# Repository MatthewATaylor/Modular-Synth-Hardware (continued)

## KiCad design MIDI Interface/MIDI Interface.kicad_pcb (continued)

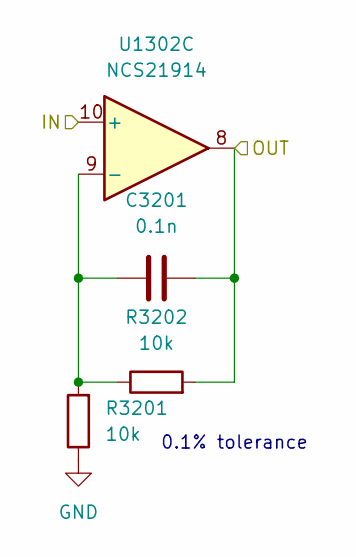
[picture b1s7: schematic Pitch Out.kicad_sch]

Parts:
C3201: 0.1n; C_Disc_D5.5mm_W2.5mm_P2.50mm
R3201, R3202: 10k; R_Axial_DIN0207_L6.3mm_D2.5mm_P7.62mm_Horizontal
U1302: NCS21914; SOIC-14_3.9x8.7mm_P1.27mm

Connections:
/Pitch/Out1/IN: U1302.5 (+); also elsewhere on the board
/Pitch/Out1/OUT: U1302.7; also elsewhere on the board
/Pitch/Out2/IN: U1302.10 (+); also elsewhere on the board
/Pitch/Out2/OUT: C3201.2, R3202.2, U1302.8; also elsewhere on the board
/Pitch/Out3/IN: U1302.12 (+); also elsewhere on the board
/Pitch/Out3/OUT: U1302.14; also elsewhere on the board
/Pitch/Out/IN: U1302.3 (+); also elsewhere on the board
/Pitch/Out/OUT: U1302.1; also elsewhere on the board
GND: R3201.1; also elsewhere on the board
unnamed 163: U1302.2 (-); also elsewhere on the board
unnamed 164: U1302.6 (-); also elsewhere on the board
unnamed: C3201.1, R3201.2, R3202.1, U1302.9 (-)
unnamed 166: U1302.13 (-); also elsewhere on the board

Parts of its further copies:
C3001, C3101, C3301, C3401, C3501, C3601, C3701: 0.1n; C_Disc_D5.5mm_W2.5mm_P2.50mm
R3001, R3002, R3101, R3102, R3301, R3302, R3401, R3402, R3501, R3502, R3601, R3602, R3701, R3702: 10k; R_Axial_DIN0207_L6.3mm_D2.5mm_P7.62mm_Horizontal

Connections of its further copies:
/Pitch/Out1/OUT: C3101.2, R3102.2; also elsewhere on the board
/Pitch/Out3/OUT: C3301.2, R3302.2; also elsewhere on the board
/Pitch/Out4/OUT: C3401.2, R3402.2; also elsewhere on the board
/Pitch/Out5/OUT: C3501.2, R3502.2; also elsewhere on the board
/Pitch/Out6/OUT: C3601.2, R3602.2; also elsewhere on the board
/Pitch/Out7/OUT: C3701.2, R3702.2; also elsewhere on the board
/Pitch/Out/OUT: C3001.2, R3002.2; also elsewhere on the board
GND: R3001.1, R3101.1, R3301.1, R3401.1, R3501.1, R3601.1, R3701.1; also elsewhere on the board
unnamed 163: C3001.1, R3001.2, R3002.1; also elsewhere on the board
unnamed 164: C3101.1, R3101.2, R3102.1; also elsewhere on the board
unnamed 166: C3301.1, R3301.2, R3302.1; also elsewhere on the board
unnamed 167: C3401.1, R3401.2, R3402.1; also elsewhere on the board
unnamed 168: C3501.1, R3501.2, R3502.1; also elsewhere on the board
unnamed 169: C3601.1, R3601.2, R3602.1; also elsewhere on the board
unnamed 170: C3701.1, R3701.2, R3702.1; also elsewhere on the board

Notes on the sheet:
0.1% tolerance

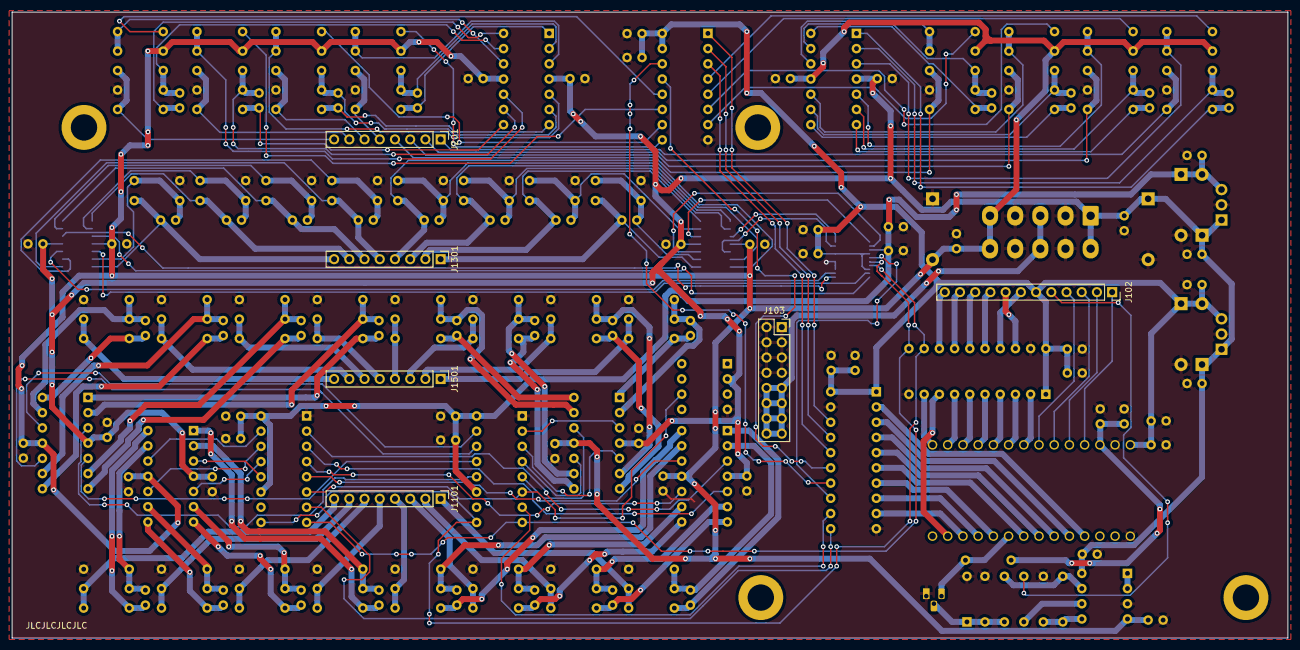
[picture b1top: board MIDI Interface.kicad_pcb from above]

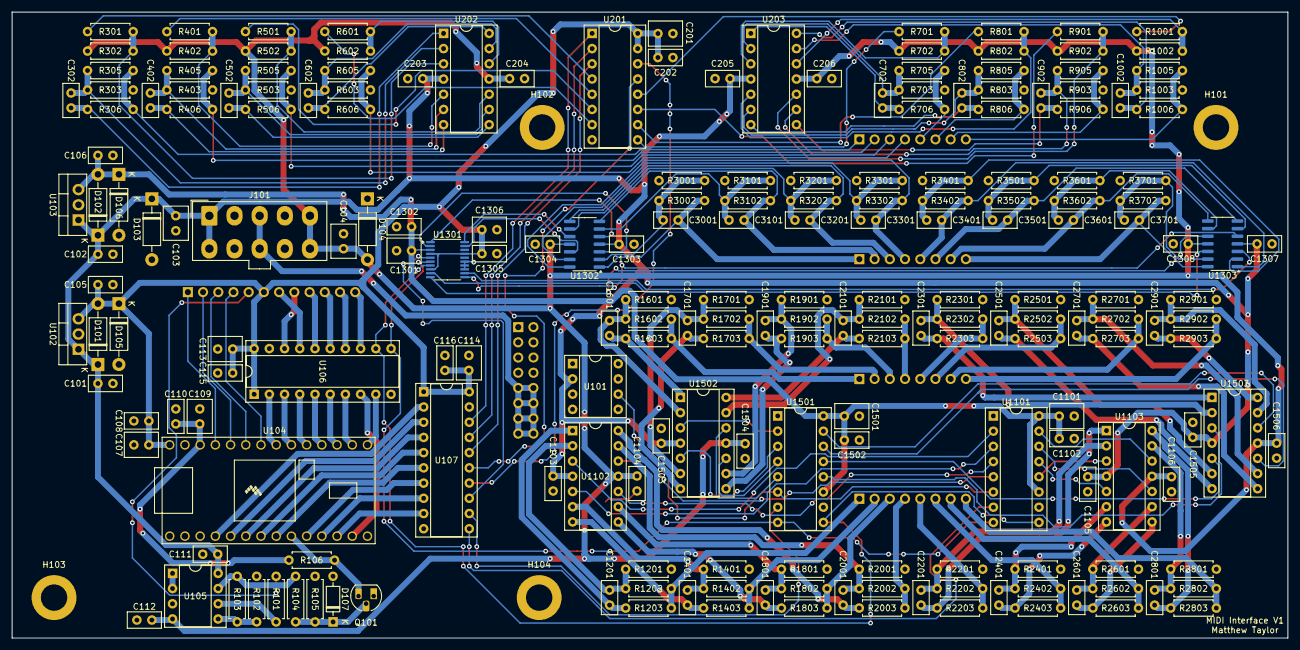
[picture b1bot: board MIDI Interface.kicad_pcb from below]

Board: 2 copper layers, 213.0 x 104.5 mm, 222 parts (216 on the bottom side), 179 nets.

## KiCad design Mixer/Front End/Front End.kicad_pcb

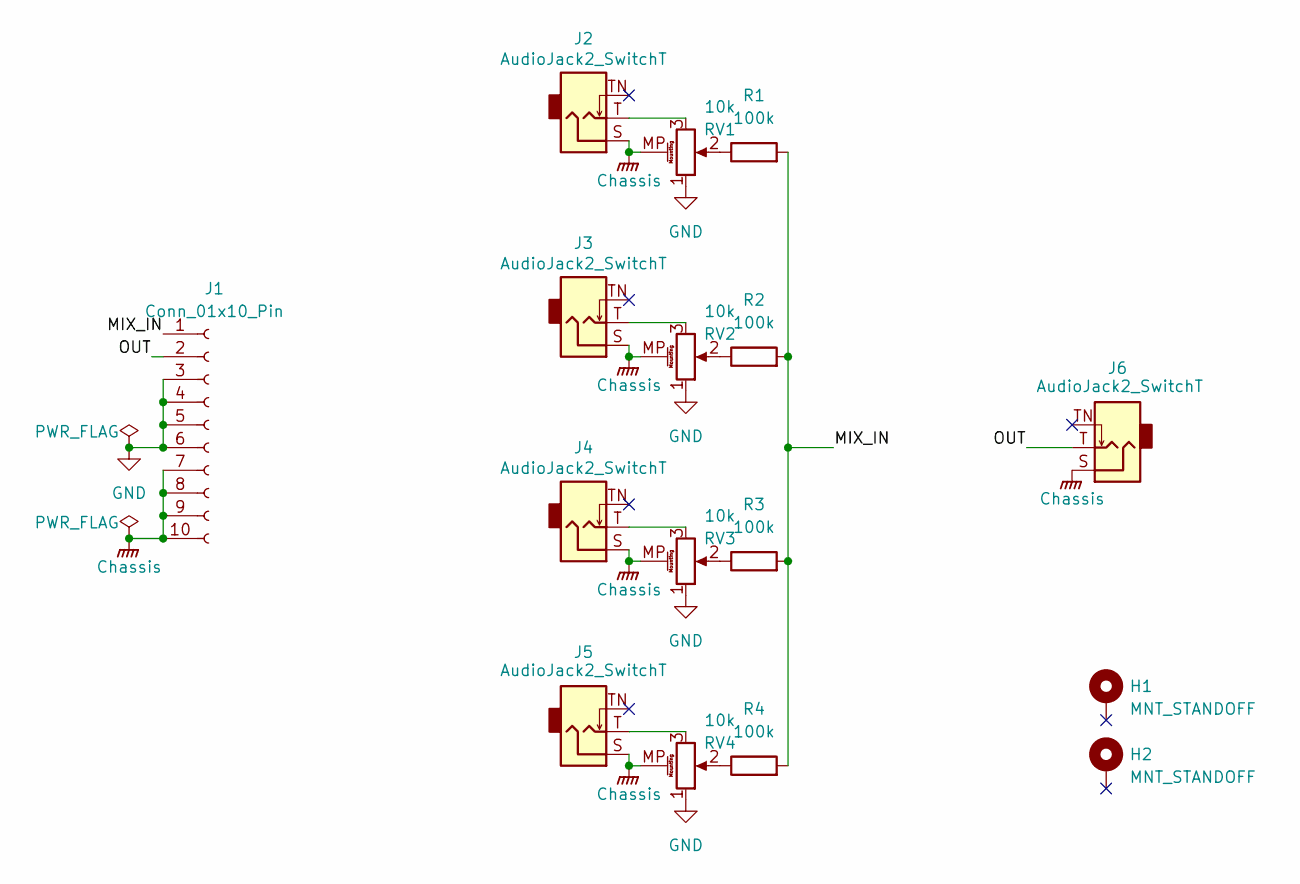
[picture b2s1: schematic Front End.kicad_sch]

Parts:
H1, H2: MNT_STANDOFF; MountingHole_Pitch7.5mm_Drill3.4mm
J1: Conn_01x10_Pin; PinSocket_1x10_P2.54mm_Vertical
J2, J3, J4, J5, J6: AudioJack2_SwitchT; Jack_3.5mm_QingPu_WQP-PJ398SM_Vertical_CircularHoles
R1, R2, R3, R4: 100k; R_Axial_DIN0207_L6.3mm_D2.5mm_P7.62mm_Horizontal
RV1, RV2, RV3, RV4: 10k; Potentiometer_Alpha_RD901F-40-00D_Single_Vertical_MP

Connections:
/MIX_IN: J1.1, R1.2, R2.2, R3.2, R4.2
/OUT: J1.2, J6.T
Chassis: J1.7, J1.8, J1.9, J1.10, J2.S, J3.S, J4.S, J5.S, J6.S, RV1.MP (MountPin), RV2.MP (MountPin), RV3.MP (MountPin), RV4.MP (MountPin)
GND: J1.3, J1.4, J1.5, J1.6, RV1.1, RV2.1, RV3.1, RV4.1
unnamed: J2.T, RV1.3
unnamed: J3.T, RV2.3
unnamed: J4.T, RV3.3
unnamed: J5.T, RV4.3
unnamed: R1.1, RV1.2
unnamed: R2.1, RV2.2
unnamed: R3.1, RV3.2
unnamed: R4.1, RV4.2

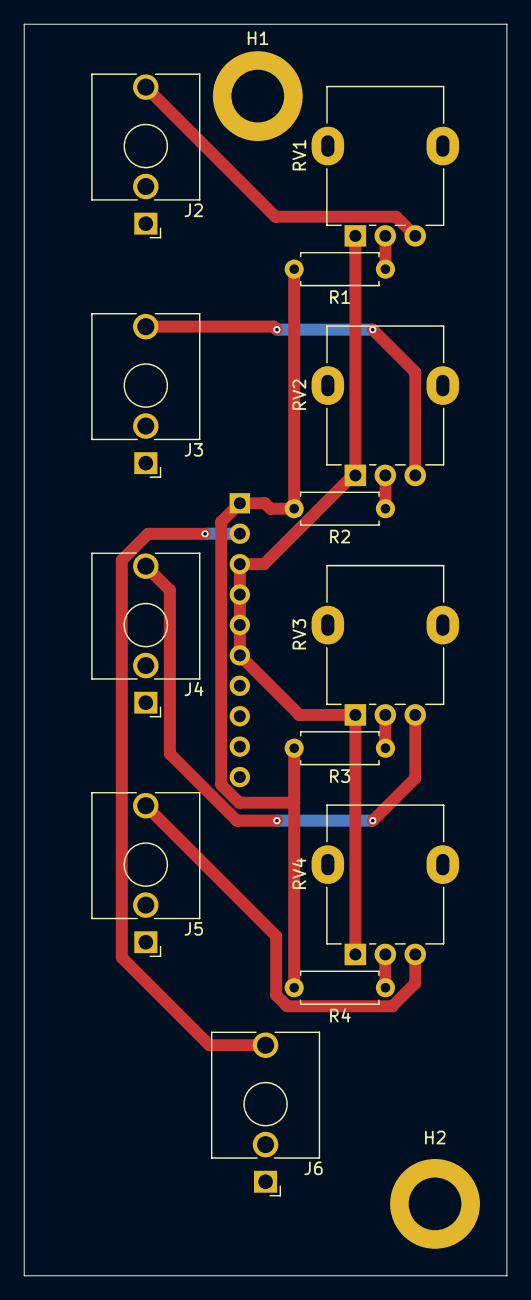
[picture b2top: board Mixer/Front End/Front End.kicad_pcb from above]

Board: 2 copper layers, 40.3 x 104.5 mm, 16 parts (1 on the bottom side), 12 nets.

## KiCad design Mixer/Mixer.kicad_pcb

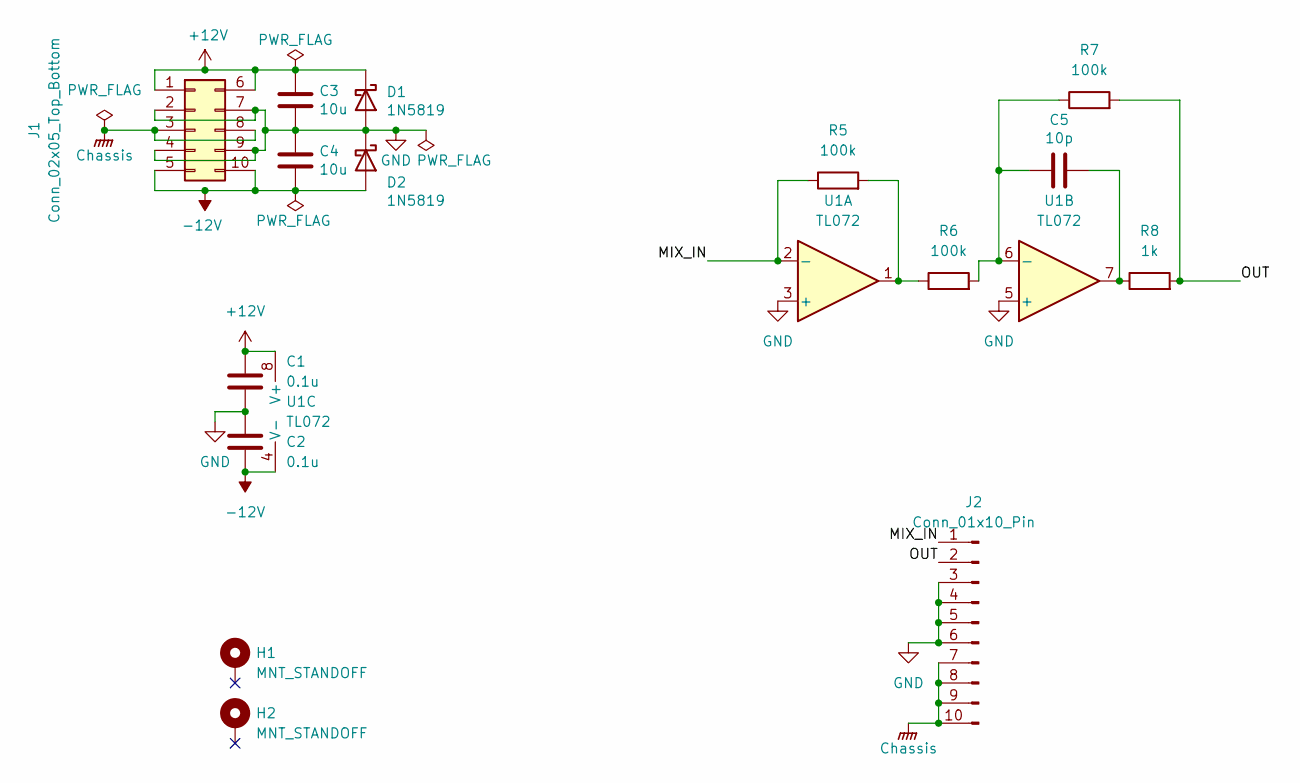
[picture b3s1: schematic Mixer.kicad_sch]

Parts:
C1, C2: 0.1u; C_Disc_D5.5mm_W2.5mm_P2.50mm
C3, C4: 10u; C_Disc_D5.5mm_W4.0mm_P2.50mm
C5: 10p; C_Disc_D5.5mm_W2.5mm_P2.50mm
D1, D2: 1N5819; D_DO-41_SOD81_P10.16mm_Horizontal
H1, H2: MNT_STANDOFF; MountingHole_Pitch7.5mm_Drill3.4mm
J1: Conn_02x05_Top_Bottom; Molex_Mini-Fit_Jr_5566-10A_2x05_P4.20mm_Vertical
J2: Conn_01x10_Pin; PinHeader_1x10_P2.54mm_Vertical
R5, R6, R7: 100k; R_Axial_DIN0207_L6.3mm_D2.5mm_P7.62mm_Horizontal
R8: 1k; R_Axial_DIN0207_L6.3mm_D2.5mm_P7.62mm_Horizontal
U1: TL072; DIP-8_W7.62mm_Socket

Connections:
+12V: C1.2, C3.1, D1.1 (K), J1.1, J1.6, U1.8 (V+)
-12V: C2.1, C4.2, D2.2 (A), J1.5, J1.10, U1.4 (V-)
/MIX_IN: J2.1, R5.1, U1.2 (-)
/OUT: J2.2, R7.2, R8.2
Chassis: J1.3, J1.8, J2.7, J2.8, J2.9, J2.10
GND: C1.1, C2.2, C3.2, C4.1, D1.2 (A), D2.1 (K), J1.2, J1.4, J1.7, J1.9, J2.3, J2.4, J2.5, J2.6, U1.3 (+), U1.5 (+)
unnamed: C5.2, R8.1, U1.7
unnamed: R5.2, R6.1, U1.1
unnamed: C5.1, R6.2, R7.1, U1.6 (-)

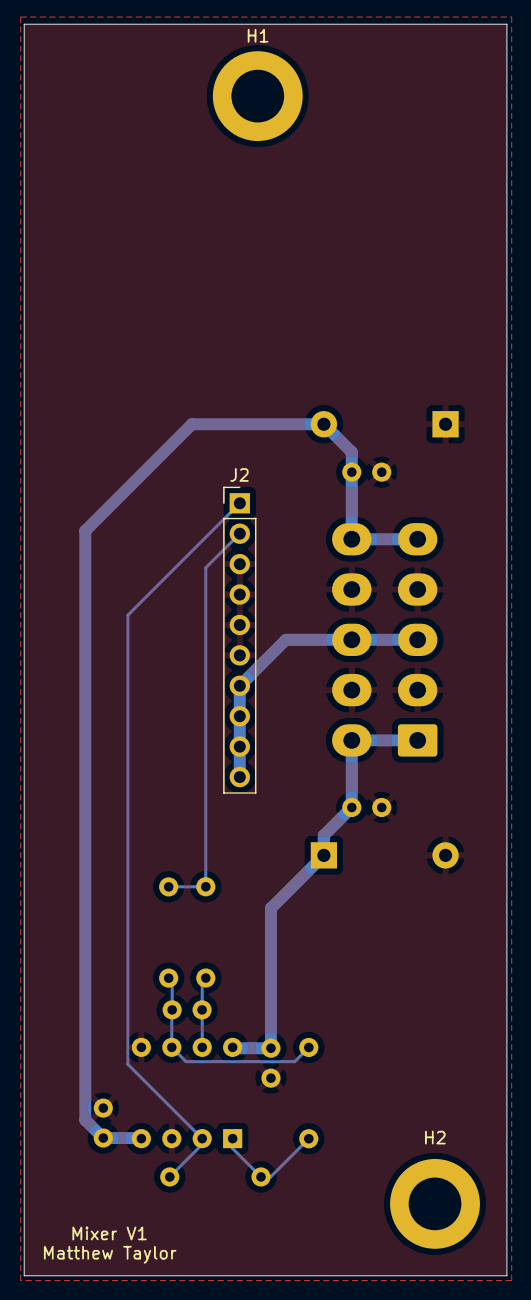
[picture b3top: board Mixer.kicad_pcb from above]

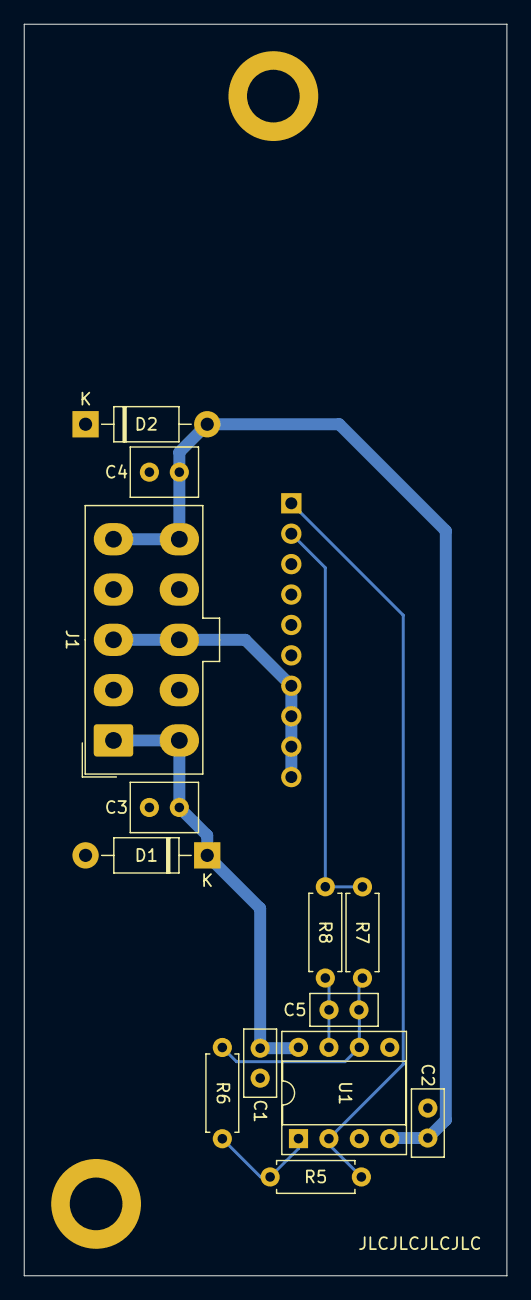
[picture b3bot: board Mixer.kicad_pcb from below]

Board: 2 copper layers, 40.3 x 104.5 mm, 16 parts (13 on the bottom side), 9 nets.

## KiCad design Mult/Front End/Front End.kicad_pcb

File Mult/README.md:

# Mult

Two buffered multiples, each with six outputs.

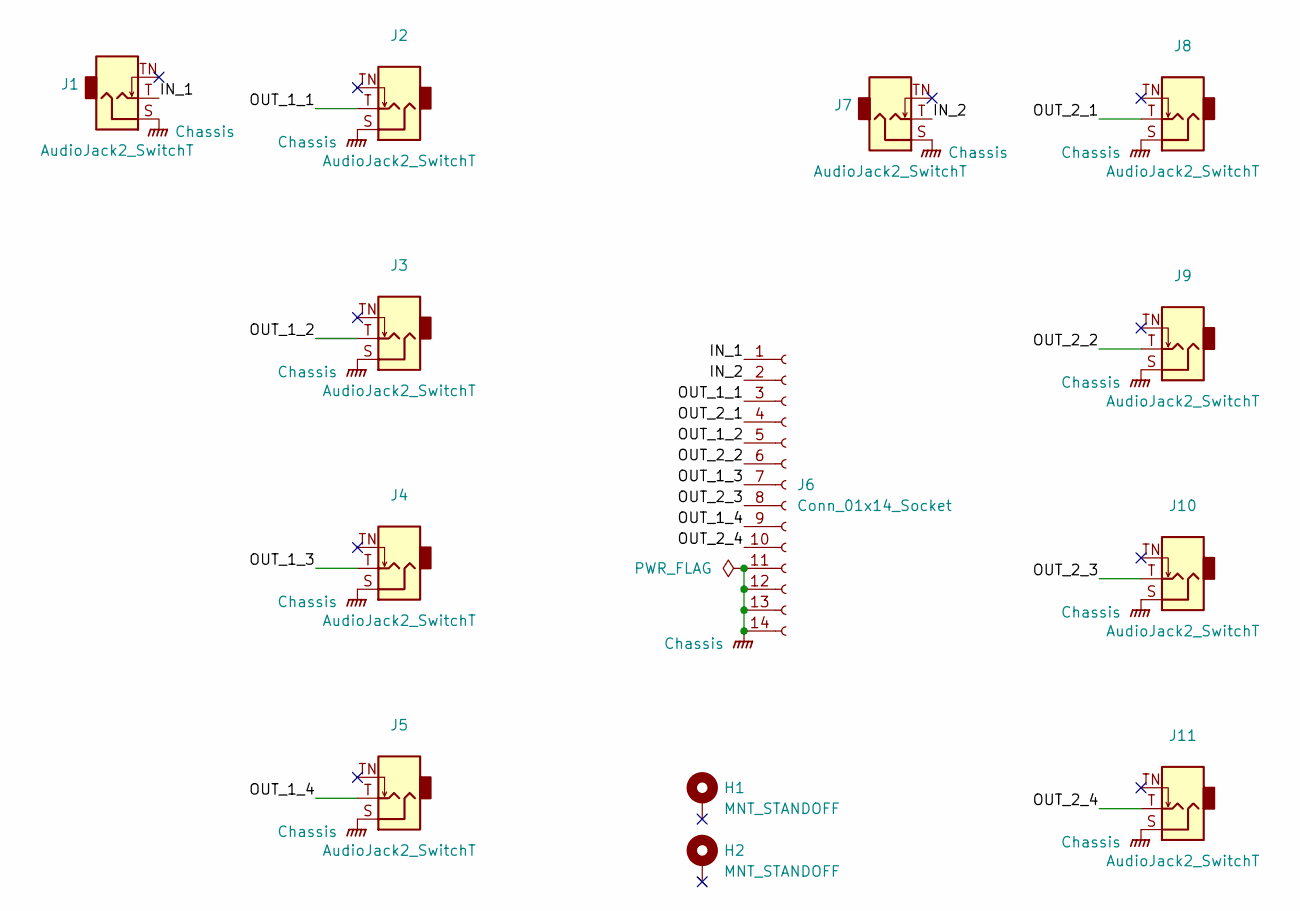
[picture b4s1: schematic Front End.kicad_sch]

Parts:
H1, H2: MNT_STANDOFF; MountingHole_Pitch7.5mm_Drill3.4mm
J1, J2, J3, J4, J5, J7, J8, J9, J10, J11: AudioJack2_SwitchT; Jack_3.5mm_QingPu_WQP-PJ398SM_Vertical_CircularHoles
J6: Conn_01x14_Socket; PinSocket_1x14_P2.54mm_Vertical

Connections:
/IN_1: J1.T, J6.1
/IN_2: J6.2, J7.T
/OUT_1_1: J2.T, J6.3
/OUT_1_2: J3.T, J6.5
/OUT_1_3: J4.T, J6.7
/OUT_1_4: J5.T, J6.9
/OUT_2_1: J6.4, J8.T
/OUT_2_2: J6.6, J9.T
/OUT_2_3: J6.8, J10.T
/OUT_2_4: J6.10, J11.T
Chassis: J1.S, J2.S, J3.S, J4.S, J5.S, J6.11, J6.12, J6.13, J6.14, J7.S, J8.S, J9.S, J10.S, J11.S

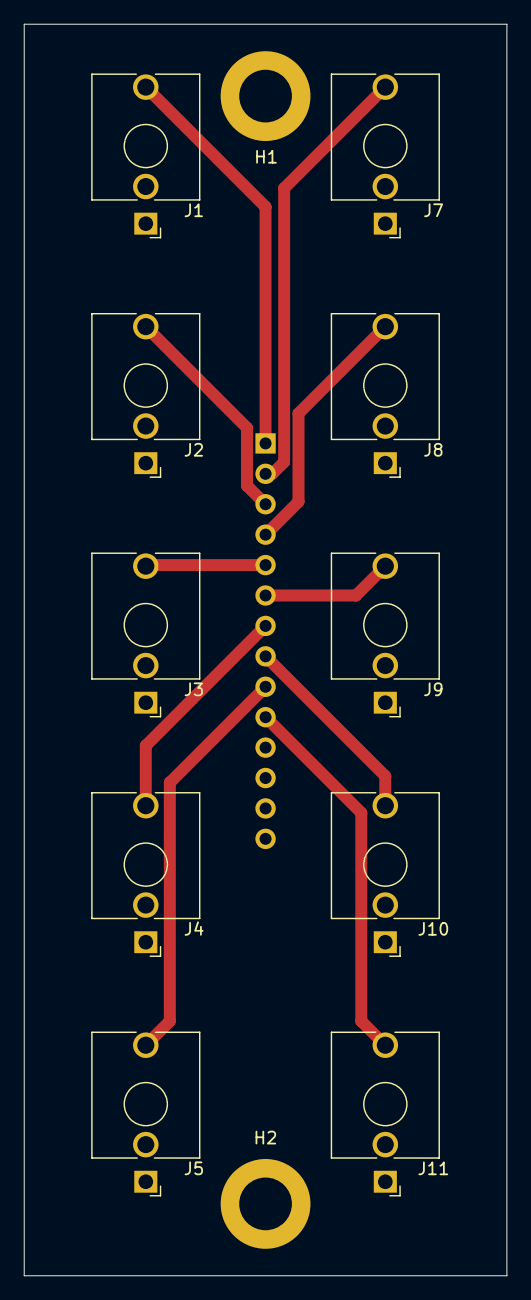
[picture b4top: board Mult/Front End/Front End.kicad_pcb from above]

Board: 2 copper layers, 40.3 x 104.5 mm, 13 parts (1 on the bottom side), 11 nets.

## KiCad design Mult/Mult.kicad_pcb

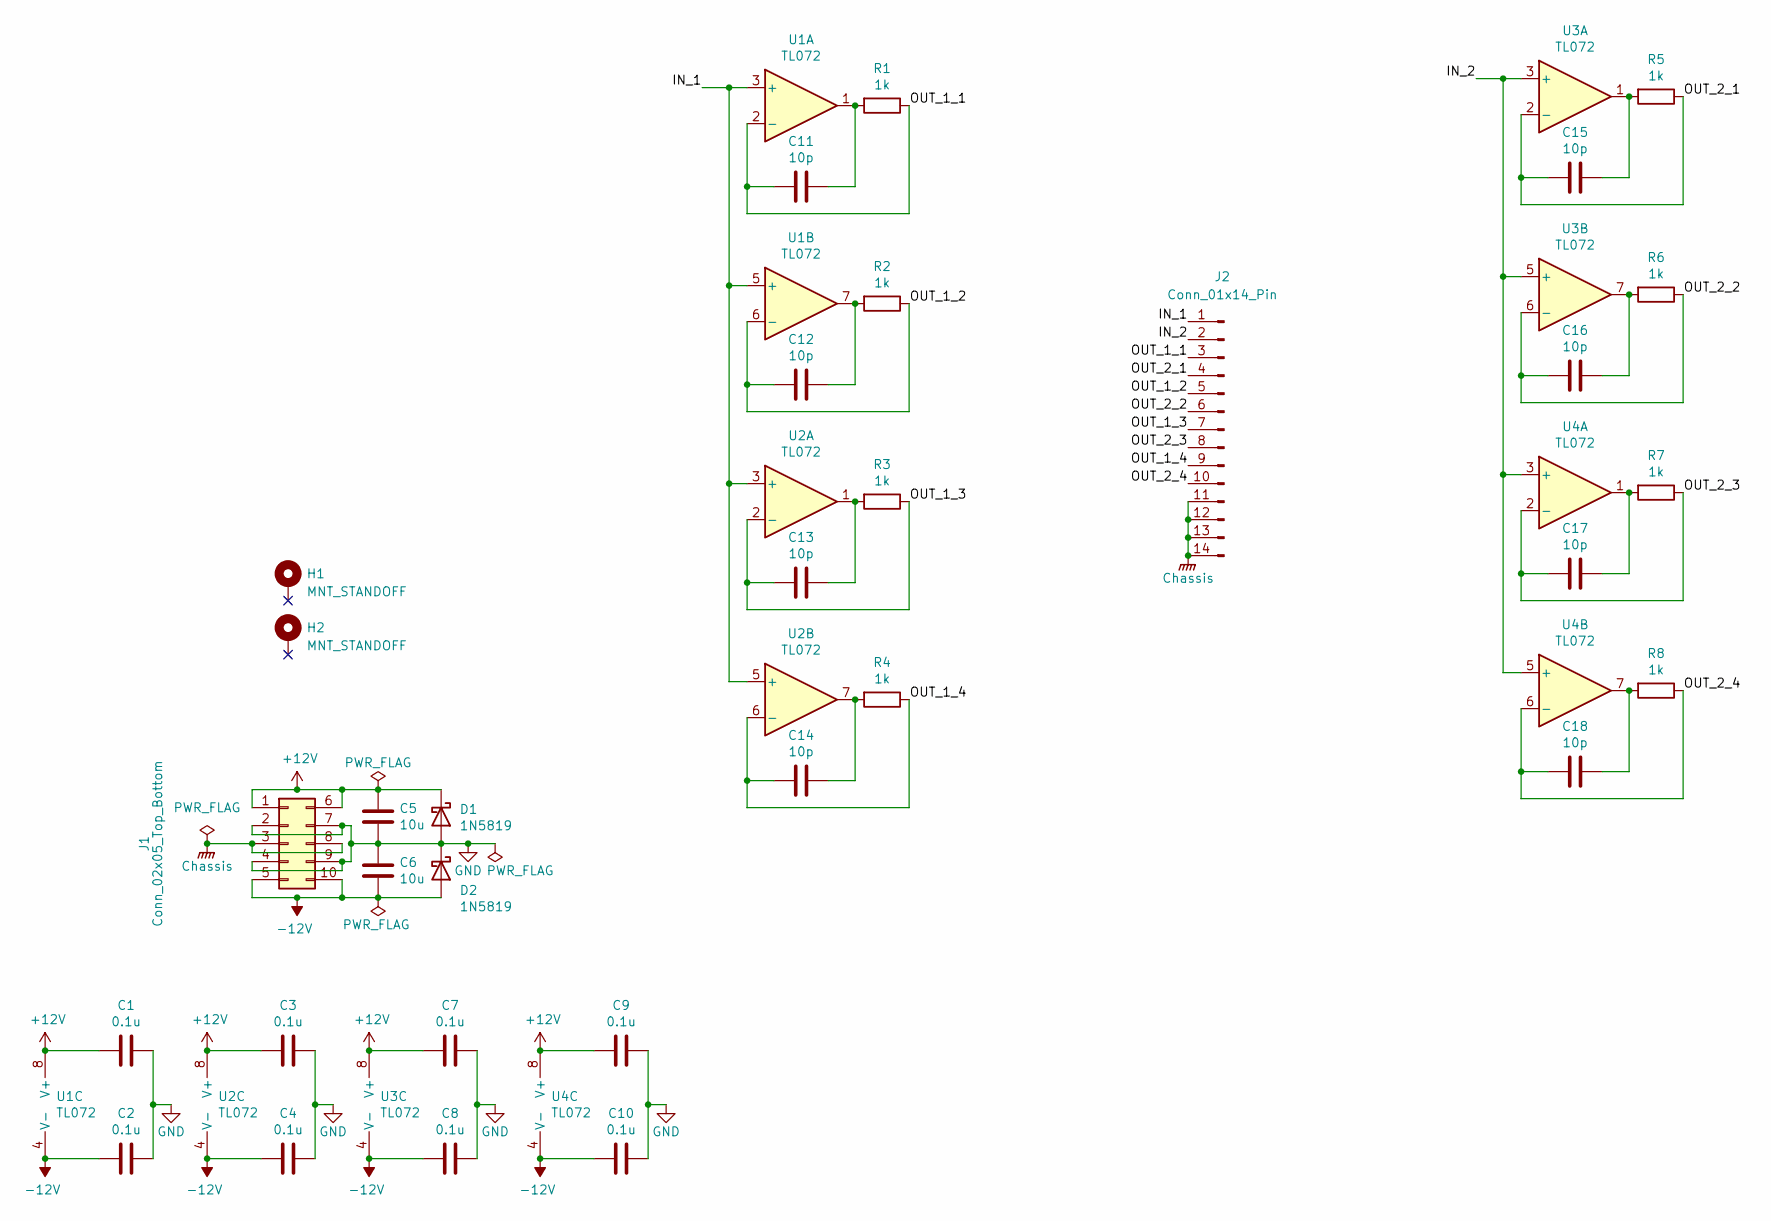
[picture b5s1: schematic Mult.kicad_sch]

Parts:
C1, C2, C3, C4, C7, C8, C9, C10: 0.1u; C_Disc_D5.5mm_W2.5mm_P2.50mm
C5, C6: 10u; C_Disc_D5.5mm_W4.0mm_P2.50mm
C11, C12, C13, C14, C15, C16, C17, C18: 10p; C_Disc_D5.5mm_W2.5mm_P2.50mm
D1, D2: 1N5819; D_DO-41_SOD81_P10.16mm_Horizontal
H1, H2: MNT_STANDOFF; MountingHole_Pitch7.5mm_Drill3.4mm
J1: Conn_02x05_Top_Bottom; Molex_Mini-Fit_Jr_5566-10A_2x05_P4.20mm_Vertical
J2: Conn_01x14_Pin; PinHeader_1x14_P2.54mm_Vertical
R1, R2, R3, R4, R5, R6, R7, R8: 1k; R_Axial_DIN0207_L6.3mm_D2.5mm_P7.62mm_Horizontal
U1, U2, U3, U4: TL072; DIP-8_W7.62mm_Socket

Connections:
+12V: C1.1, C3.1, C5.1, C7.1, C9.1, D1.1 (K), J1.1, J1.6, U1.8 (V+), U2.8 (V+), U3.8 (V+), U4.8 (V+)
-12V: C2.1, C4.1, C6.2, C8.1, C10.1, D2.2 (A), J1.5, J1.10, U1.4 (V-), U2.4 (V-), U3.4 (V-), U4.4 (V-)
/IN_1: J2.1, U1.3 (+), U1.5 (+), U2.3 (+), U2.5 (+)
/IN_2: J2.2, U3.3 (+), U3.5 (+), U4.3 (+), U4.5 (+)
/OUT_1_1: C11.1, J2.3, R1.1, U1.2 (-)
/OUT_1_2: C12.1, J2.5, R2.1, U1.6 (-)
/OUT_1_3: C13.1, J2.7, R3.1, U2.2 (-)
/OUT_1_4: C14.1, J2.9, R4.1, U2.6 (-)
/OUT_2_1: C15.1, J2.4, R5.1, U3.2 (-)
/OUT_2_2: C16.1, J2.6, R6.1, U3.6 (-)
/OUT_2_3: C17.1, J2.8, R7.1, U4.2 (-)
/OUT_2_4: C18.1, J2.10, R8.1, U4.6 (-)
Chassis: J1.3, J1.8, J2.11, J2.12, J2.13, J2.14
GND: C1.2, C2.2, C3.2, C4.2, C5.2, C6.1, C7.2, C8.2, C9.2, C10.2, D1.2 (A), D2.1 (K), J1.2, J1.4, J1.7, J1.9
unnamed: C11.2, R1.2, U1.1
unnamed: C12.2, R2.2, U1.7
unnamed: C13.2, R3.2, U2.1
unnamed: C14.2, R4.2, U2.7
unnamed: C15.2, R5.2, U3.1
unnamed: C16.2, R6.2, U3.7
unnamed: C17.2, R7.2, U4.1
unnamed: C18.2, R8.2, U4.7

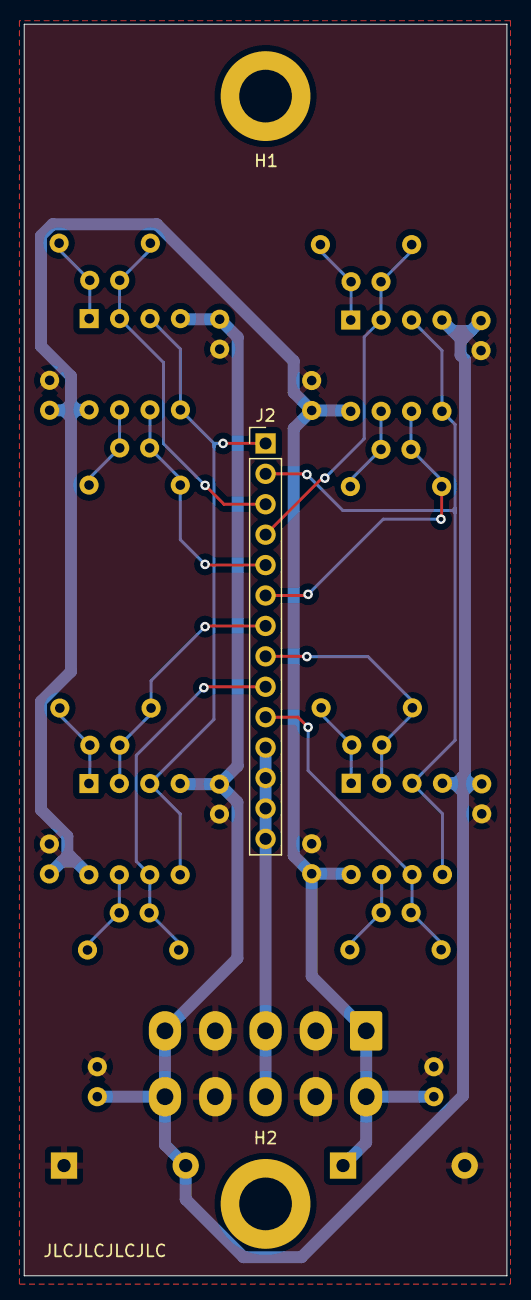
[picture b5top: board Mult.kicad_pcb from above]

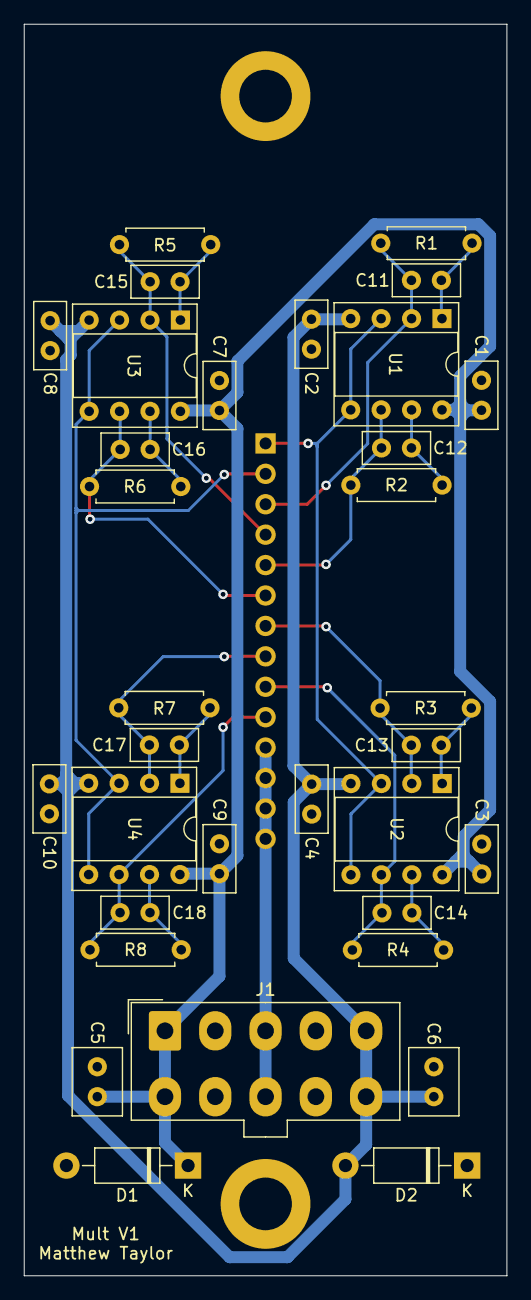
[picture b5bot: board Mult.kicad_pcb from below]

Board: 2 copper layers, 40.3 x 104.5 mm, 36 parts (33 on the bottom side), 22 nets.
